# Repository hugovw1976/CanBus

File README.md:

# CanBus
Wireless Control CanBus Electrical System for 1976 VW Bug.
NRF24L01 With ATmega328p Wireless control for car electrical system.
Transmitter run on ATmega 328p running on low power mode 1mhz: https://forum.mysensors.org/topic/3018/tutorial-how-to-burn-1mhz-8mhz-bootloader-using-arduino-ide-1-6-5-r5/2
Receiver run on Teensy 3.2 with SN65HVD230 transceiver, module communicate with front/rear/midle modules over CanBus
CanBus Modules run on Teensy 3.2 with SN65HVD230 transceiver.
Wiper control over LinBus (motor from BMW) LIN library from: https://github.com/gandrewstone/LIN/blob/master/LIN.ino
  
  Transmitter:

<a data-flickr-embed="true" data-context="true"  href="https://www.flickr.com/photos/r42bug/39444284152/in/dateposted/" title="20171224_134232">

Receiver:

Can modules:

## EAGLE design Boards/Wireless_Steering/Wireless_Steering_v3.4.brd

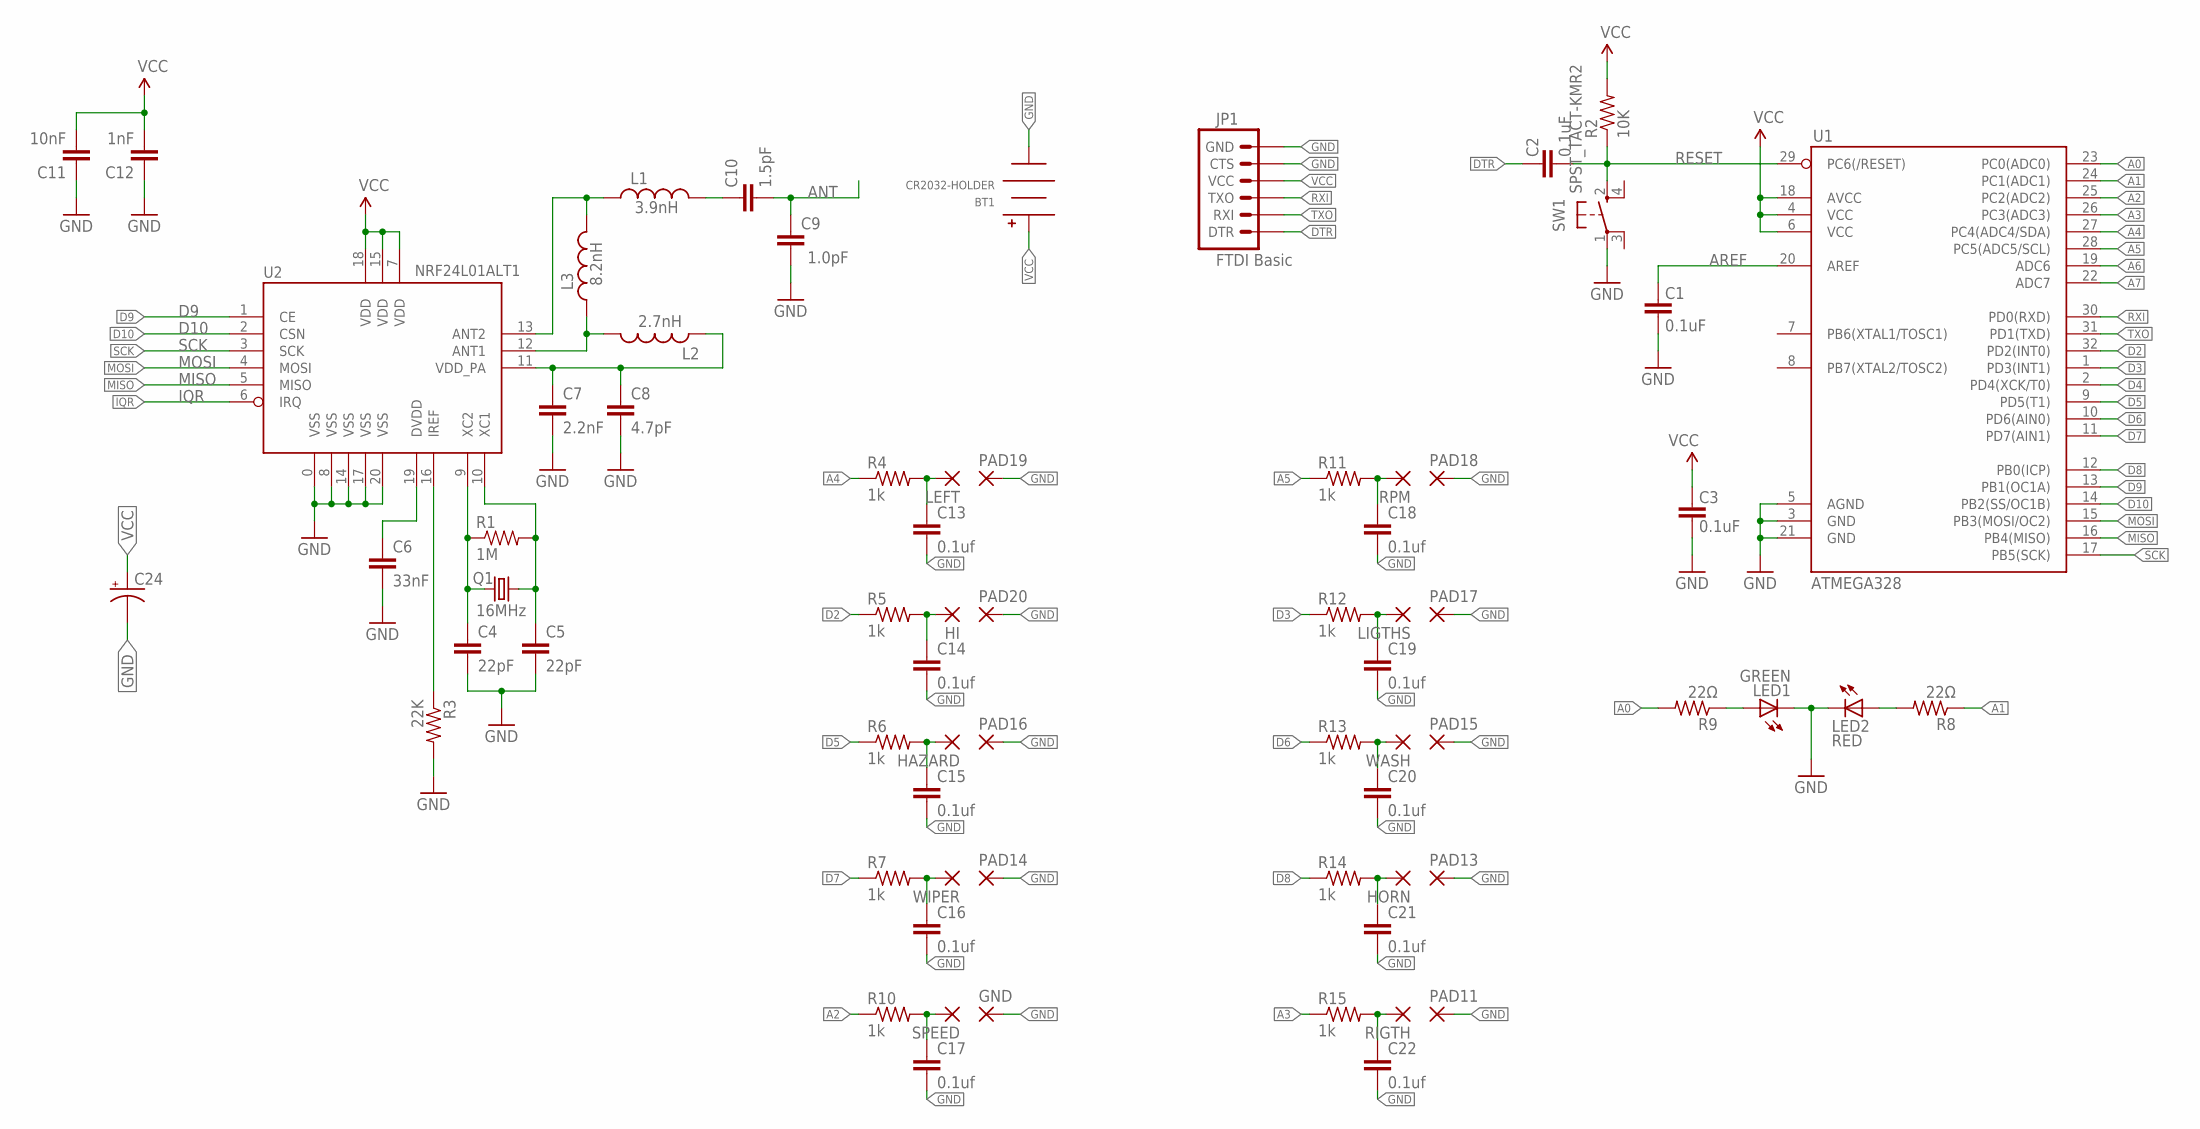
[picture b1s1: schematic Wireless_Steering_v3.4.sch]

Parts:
BT1: CR2032-HOLDER; CH28-2032LF
C1, C2, C3: 0.1uF; 0402-CAP
C4, C5: 22pF; 0402-CAP
C6: 33nF; 0402-CAP
C7: 2.2nF; 0402-CAP
C8: 4.7pF; 0402-CAP
C9: 1.0pF; 0402-CAP
C10: 1.5pF; 0402-CAP
C11: 10nF; 0402-CAP
C12: 1nF; 0402-CAP
C13, C14, C15, C16, C17, C18, C19, C20, C21, C22: 0.1uf; 0402-CAP
C24: CAP_POL1206; EIA3216
GND: SMD2; SMD1,27-2,54
HAZARD: SMD2; SMD1,27-2,54
HI: SMD2; SMD1,27-2,54
HORN: SMD2; SMD1,27-2,54
JP1: FTDI Basic; 1X06
L1: 3.9nH; C0402
L2: 2.7nH; C0402
L3: 8.2nH; C0402
LED1: GREEN; CHIP-LED0603
LED2: RED; CHIP-LED0603
LEFT: SMD2; SMD1,27-2,54
LIGTHS: SMD2; SMD1,27-2,54
PAD11, PAD13, PAD14, PAD15, PAD16, PAD17, PAD18, PAD19, PAD20: SMD2; SMD1,27-2,54
Q1: 16MHz; CRYSTAL-SMD-5X3
R1: 1M; 0402-RES
R2: 10K; 0402-RES
R3: 22K; 0402-RES
R4, R5, R6, R7, R10, R11, R12, R13, R14, R15: 1k; R0402
R8, R9: 22Ω; R0402
RIGTH: SMD2; SMD1,27-2,54
RPM: SMD2; SMD1,27-2,54
SPEED: SMD2; SMD1,27-2,54
SW1: SPST_TACT-KMR2; KMR2
U1: ATMEGA328; TQFP32-08
U2: NRF24L01ALT1; QFN20_ALT1
WASH: SMD2; SMD1,27-2,54
WIPER: SMD2; SMD1,27-2,54

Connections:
A0: R9.2, U1.23 (PC0(ADC0))
A1: R8.1, U1.24 (PC1(ADC1))
A2: R10.1, U1.25 (PC2(ADC2))
A3: R15.1, U1.26 (PC3(ADC3))
A4: R4.1, U1.27 (PC4(ADC4/SDA))
A5: R11.1, U1.28 (PC5(ADC5/SCL))
A6: U1.19 (ADC6)
A7: U1.22 (ADC7)
ANT: C9.2, C10.2
AREF: C1.2, U1.20 (AREF)
D2: R5.1, U1.32 (PD2(INT0))
D3: R12.1, U1.1 (PD3(INT1))
D4: U1.2 (PD4(XCK/T0))
D5: R6.1, U1.9 (PD5(T1))
D6: R13.1, U1.10 (PD6(AIN0))
D7: R7.1, U1.11 (PD7(AIN1))
D8: R14.1, U1.12 (PB0(ICP))
D9: U1.13 (PB1(OC1A)), U2.1 (CE)
D10: U1.14 (PB2(SS/OC1B)), U2.2 (CSN)
DTR: C2.2, JP1.1 (DTR)
GND: BT1.NEG, C1.1, C3.1, C4.2, C5.2, C6.2, C7.2, C8.2, C9.1, C11.1, C12.1, C13.2, C14.2, C15.2, C16.2, C17.2, C18.2, C19.2, C20.2, C21.2, C22.2, C24.C (-), GND.1, JP1.5 (CTS), JP1.6 (GND), LED1.C, LED2.C, PAD11.1, PAD13.1, PAD14.1, PAD15.1, PAD16.1, PAD17.1, PAD18.1, PAD19.1, PAD20.1, R3.2, SW1.1, U1.3 (GND), U1.5 (AGND), U1.21 (GND), U2.0 (VSS), U2.8 (VSS), U2.14 (VSS), U2.17 (VSS), U2.20 (VSS)
IQR: U2.6 (IRQ)
MISO: U1.16 (PB4(MISO)), U2.5 (MISO)
MOSI: U1.15 (PB3(MOSI/OC2)), U2.4 (MOSI)
unnamed: C4.1, Q1.1, R1.1, U2.9 (XC2)
unnamed: C5.1, Q1.3 (2), R1.2, U2.10 (XC1)
unnamed: L1.1, L3.2, U2.13 (ANT2)
unnamed: LED2.A, R8.2
unnamed: LED1.A, R9.1
unnamed: C7.1, C8.1, L2.1, U2.11 (VDD_PA)
unnamed: R3.1, U2.16 (IREF)
unnamed: C6.1, U2.19 (DVDD)
unnamed: L2.2, L3.1, U2.12 (ANT1)
unnamed: C10.1, L1.2
unnamed: C13.1, LEFT.1, R4.2
unnamed: C14.1, HI.1, R5.2
unnamed: C16.1, R7.2, WIPER.1
unnamed: C17.1, R10.2, SPEED.1
unnamed: C22.1, R15.2, RIGTH.1
unnamed: C21.1, HORN.1, R14.2
unnamed: C20.1, R13.2, WASH.1
unnamed: C19.1, LIGTHS.1, R12.2
unnamed: C18.1, R11.2, RPM.1
unnamed: C15.1, HAZARD.1, R6.2
RESET: C2.1, R2.1, SW1.2 (S), U1.29 (PC6(/RESET))
RXI: JP1.3 (TXO), U1.30 (PD0(RXD))
SCK: U1.17 (PB5(SCK)), U2.3 (SCK)
TXO: JP1.2 (RXI), U1.31 (PD1(TXD))
VCC: BT1.POS, C3.2, C11.2, C12.2, C24.A (+), JP1.4 (VCC), R2.2, U1.4 (VCC), U1.6 (VCC), U1.18 (AVCC), U2.7 (VDD), U2.15 (VDD), U2.18 (VDD)

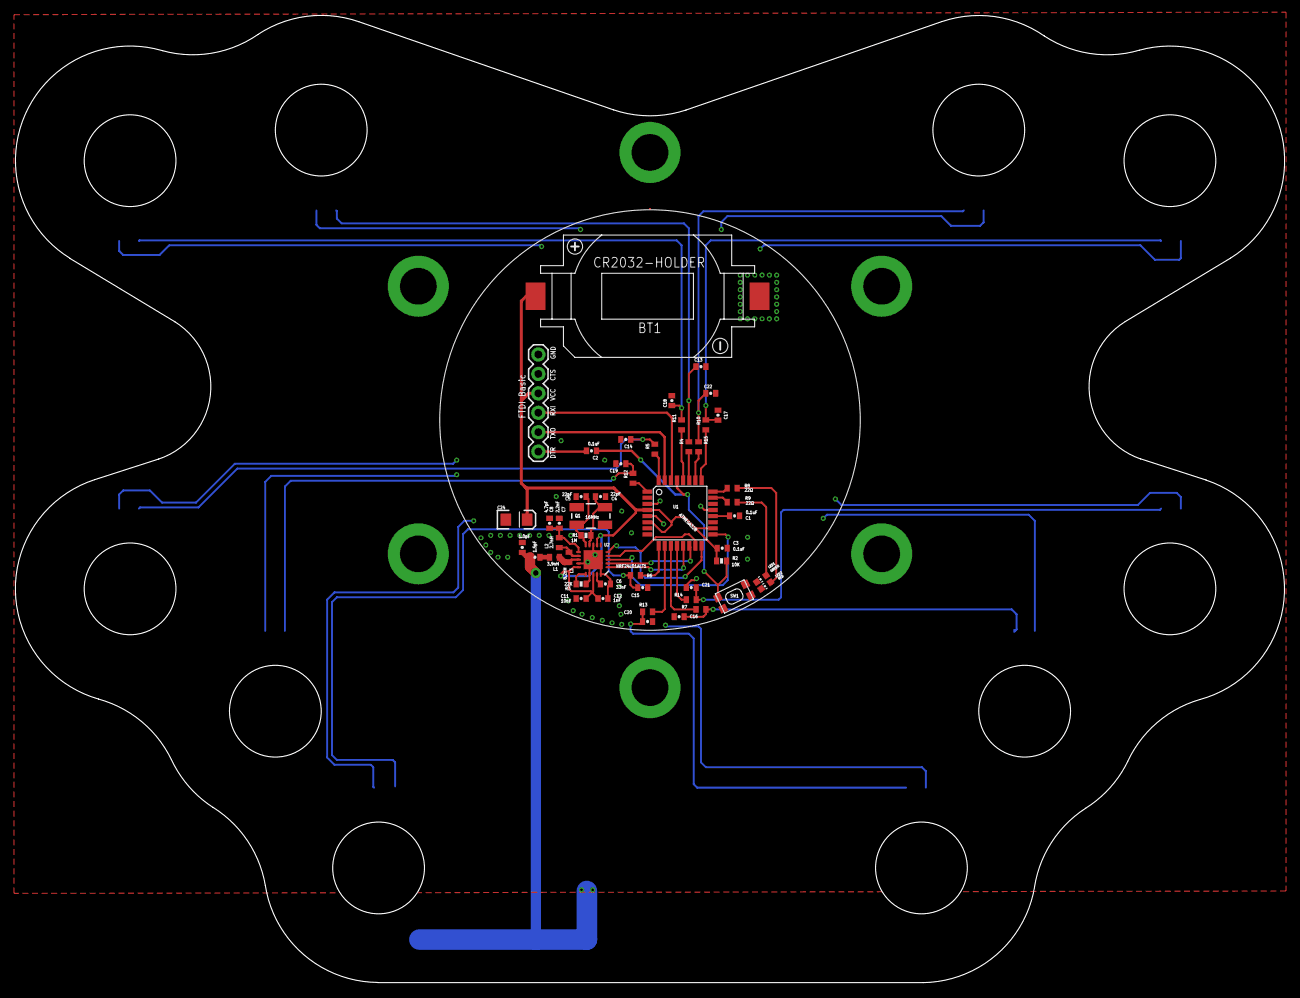
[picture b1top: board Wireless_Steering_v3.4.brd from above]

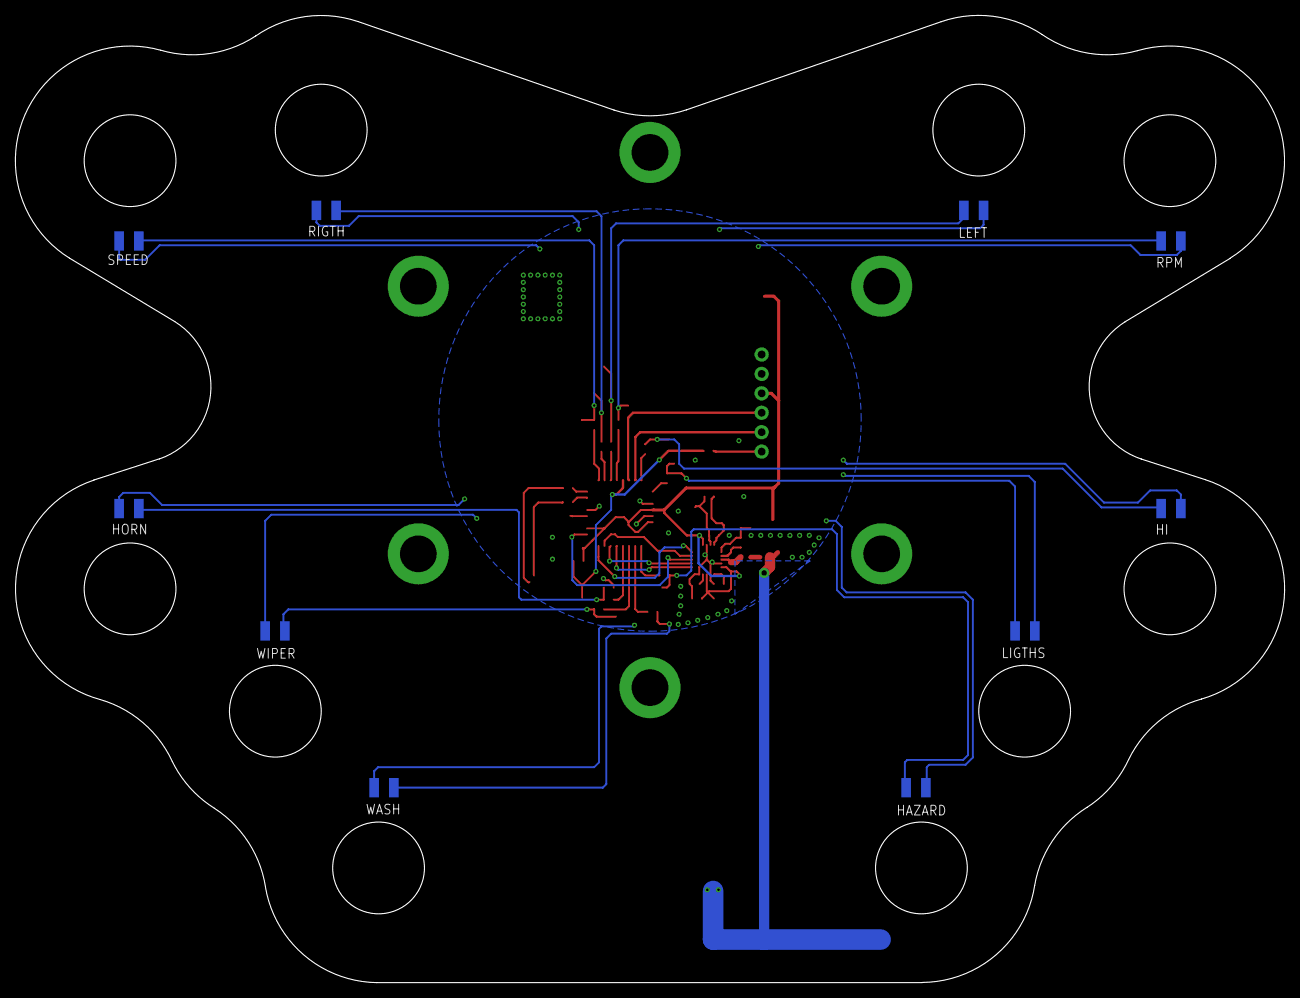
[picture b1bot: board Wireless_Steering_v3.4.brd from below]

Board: 2 copper layers, 166.0 x 126.5 mm, 69 parts (20 on the bottom side), 45 nets.

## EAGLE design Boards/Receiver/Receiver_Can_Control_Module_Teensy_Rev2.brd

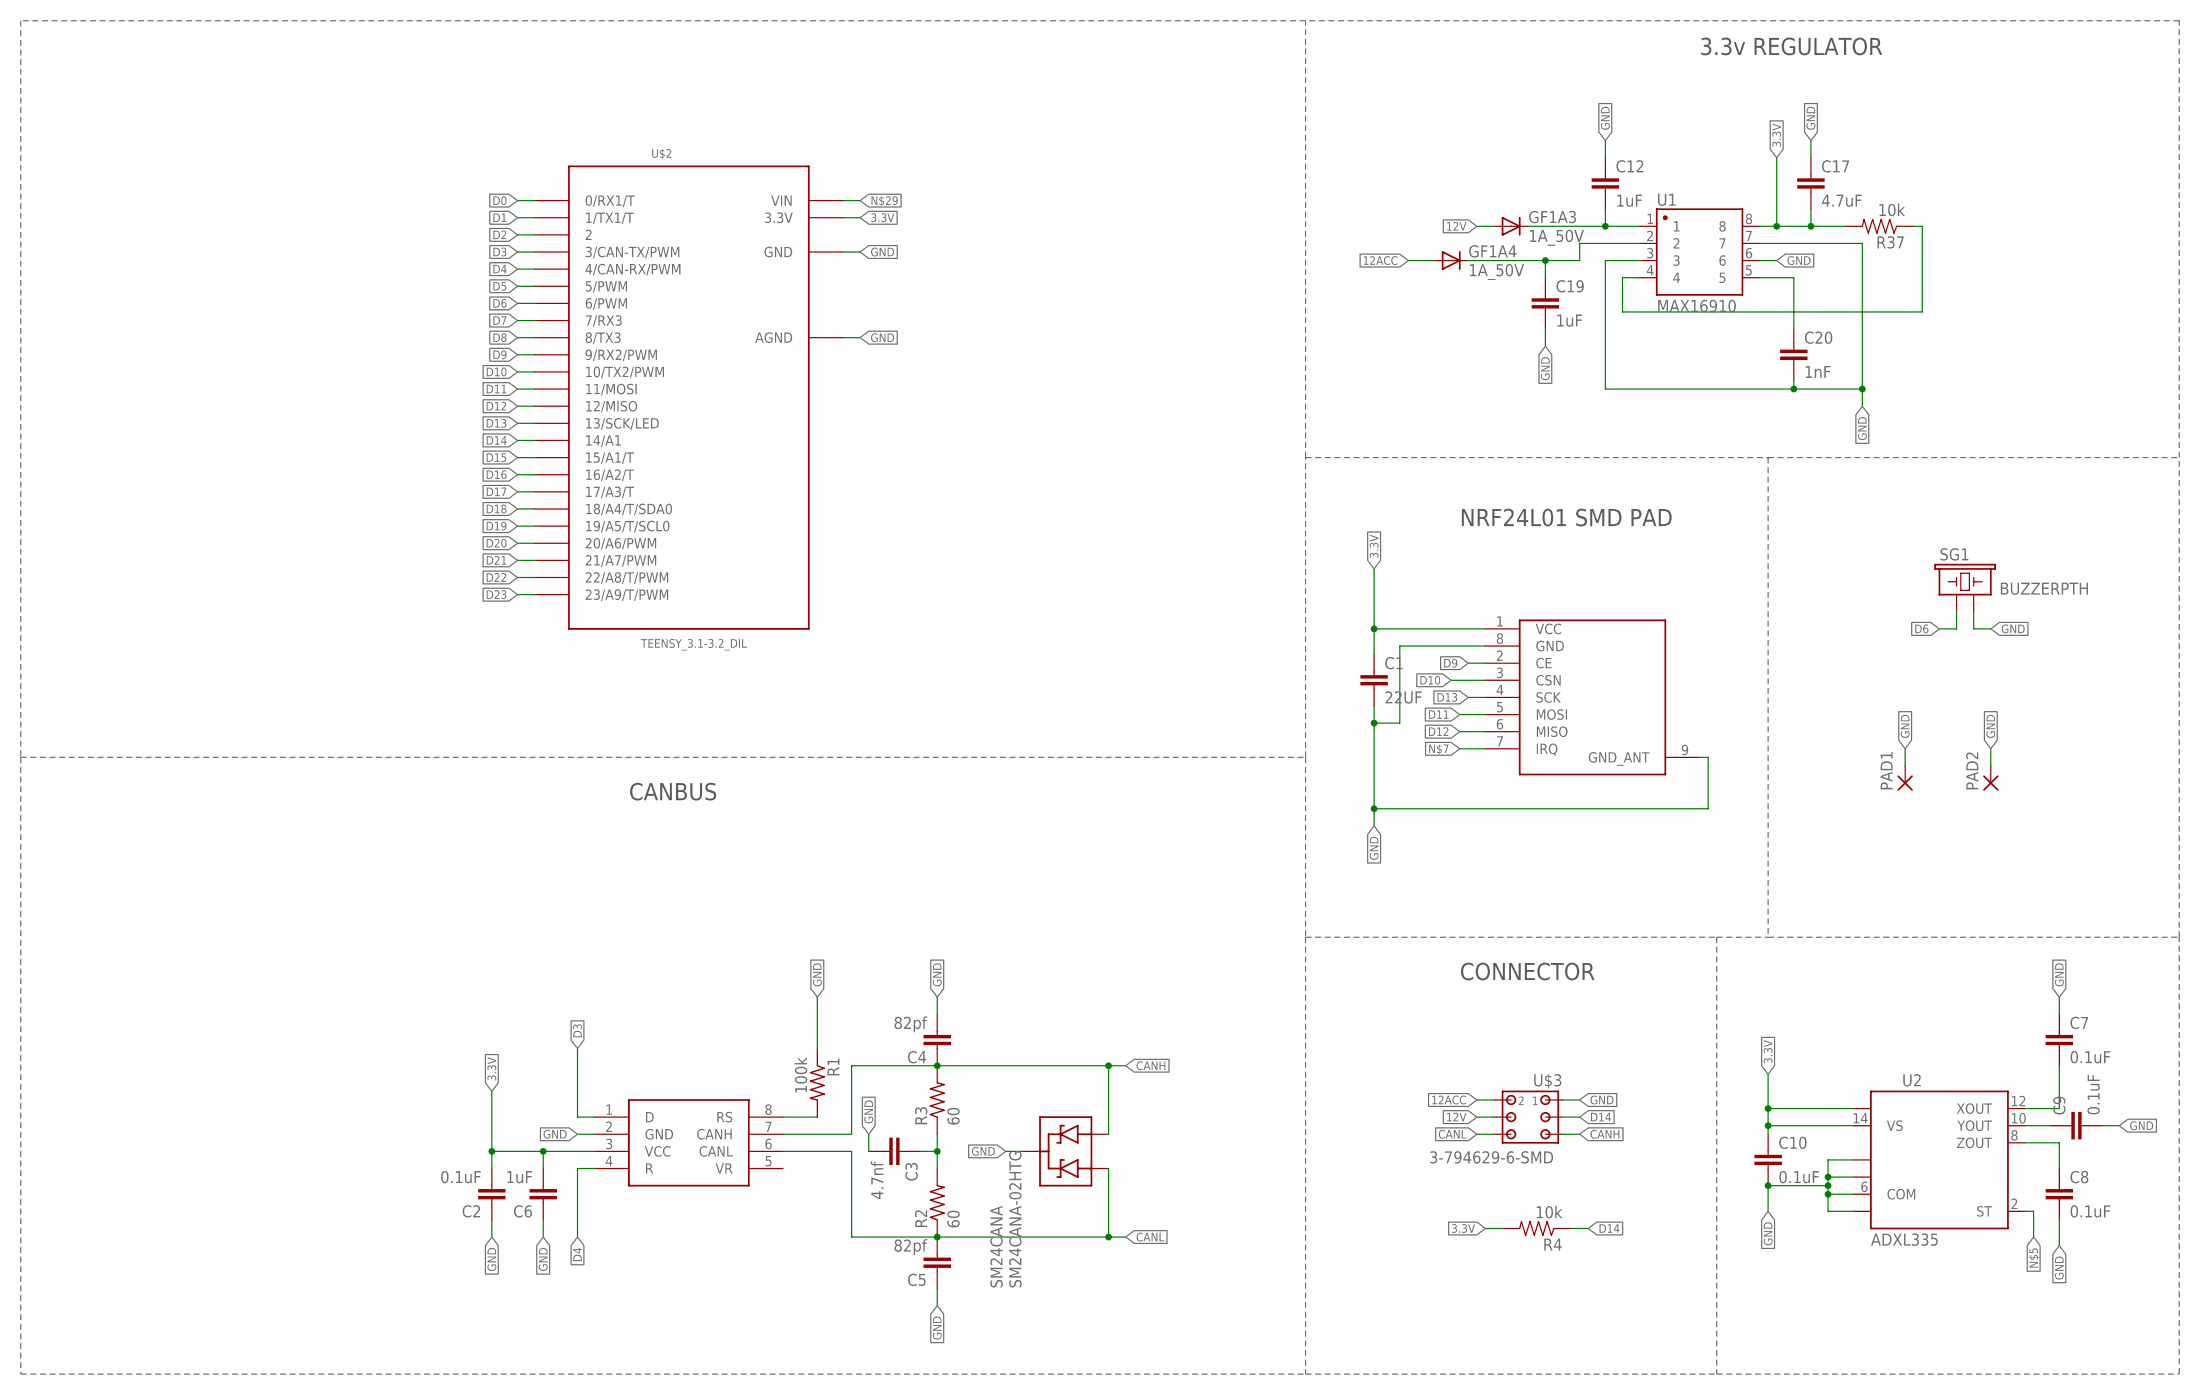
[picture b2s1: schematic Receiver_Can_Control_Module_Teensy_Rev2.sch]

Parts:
C1: 22UF; 1206
C2, C7, C8, C9, C10: 0.1uF; 0603-CAP
C3: 4.7nf; 0603-CAP
C4, C5: 82pf; 0603-CAP
C6: 1uF; 0603-CAP
C12, C19: 1uF; 0805
C17: 4.7uF; 0805
C20: 1nF; 0805
GF1A3, GF1A4: 1A_50V; DO-214AC
PAD1, PAD2: SMD2; SMD1,27-2,54
R1: 100k; R0402
R2, R3: 60; R0402
R4, R37: 10k; 0603-RES
SG1: BUZZERPTH; BUZZER-12MM
SM24CANA: SM24CANA-02HTG; SOT23-3
U1: MAX16910; SO08
U2: ADXL335; LFCSP-16
U$1: NRF24L01_PAD2; NRF24-2
U$2: TEENSY_3.1-3.2_DIL; TEENSY_3.0-3.2&LC_DIL
U$3: 3-794629-6-SMD; 3-794629-6
VP230: UP230; SO08

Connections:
3.3V: C1.1, C2.2, C6.2, C10.1, C17.2, R4.2, R37.2, U1.8, U2.14 (VS), U2.15 (VS), U$1.1 (VCC), U$2.3.3V, VP230.3 (VCC)
12ACC: GF1A4.A, U$3.2
12V: GF1A3.A, U$3.4
CANH: C4.1, R3.2, SM24CANA.2 (A2), U$3.5, VP230.7 (CANH)
CANL: C5.2, R2.1, SM24CANA.1 (A1), U$3.6, VP230.6 (CANL)
D0: U$2.0 (0/RX1/T)
D1: U$2.1 (1/TX1/T)
D2: U$2.2
D3: U$2.3 (3/CAN-TX/PWM), VP230.1 (D)
D4: U$2.4 (4/CAN-RX/PWM), VP230.4 (R)
D5: U$2.5 (5/PWM)
D6: SG1.+ (1), U$2.6 (6/PWM)
D7: U$2.7 (7/RX3)
D8: U$2.8 (8/TX3)
D9: U$1.2 (CE), U$2.9 (9/RX2/PWM)
D10: U$1.3 (CSN), U$2.10 (10/TX2/PWM)
D11: U$1.5 (MOSI), U$2.11 (11/MOSI)
D12: U$1.6 (MISO), U$2.12 (12/MISO)
D13: U$1.4 (SCK), U$2.13 (13/SCK/LED)
D14: R4.1, U$2.14/A0 (14/A1), U$3.3
D15: U$2.15/A1 (15/A1/T)
D16: U$2.16/A2 (16/A2/T)
D17: U$2.17/A3 (17/A3/T)
D18: U$2.18/A4 (18/A4/T/SDA0)
D19: U$2.19/A5 (19/A5/T/SCL0)
D20: U$2.20/A6 (20/A6/PWM)
D21: C7.2, U2.12 (XOUT), U$2.21/A7 (21/A7/PWM)
D22: C9.1, U2.10 (YOUT), U$2.22/A8 (22/A8/T/PWM)
D23: C8.1, U2.8 (ZOUT), U$2.23/A9 (23/A9/T/PWM)
GND: C1.2, C2.1, C3.2, C4.2, C5.1, C6.1, C7.1, C8.2, C9.2, C10.2, C12.1, C17.1, C19.2, C20.2, PAD1.1, PAD2.1, R1.1, SG1.- (2), SM24CANA.3 (C), U1.3, U1.6, U1.7, U2.3 (COM), U2.5 (COM), U2.6 (COM), U2.7 (COM), U$1.8 (GND), U$1.9 (GND_ANT), U$2.AGND, U$2.GND, U$3.1, VP230.2 (GND)
unnamed: C12.2, GF1A3.C, U1.1
unnamed: C19.1, GF1A4.C, U1.2
unnamed: R37.1, U1.4
unnamed: C20.1, U1.5
unnamed: R1.2, VP230.8 (RS)
unnamed: C3.1, R2.2, R3.1

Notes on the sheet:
CANBUS
CONNECTOR
NRF24L01 SMD PAD
3.3v REGULATOR

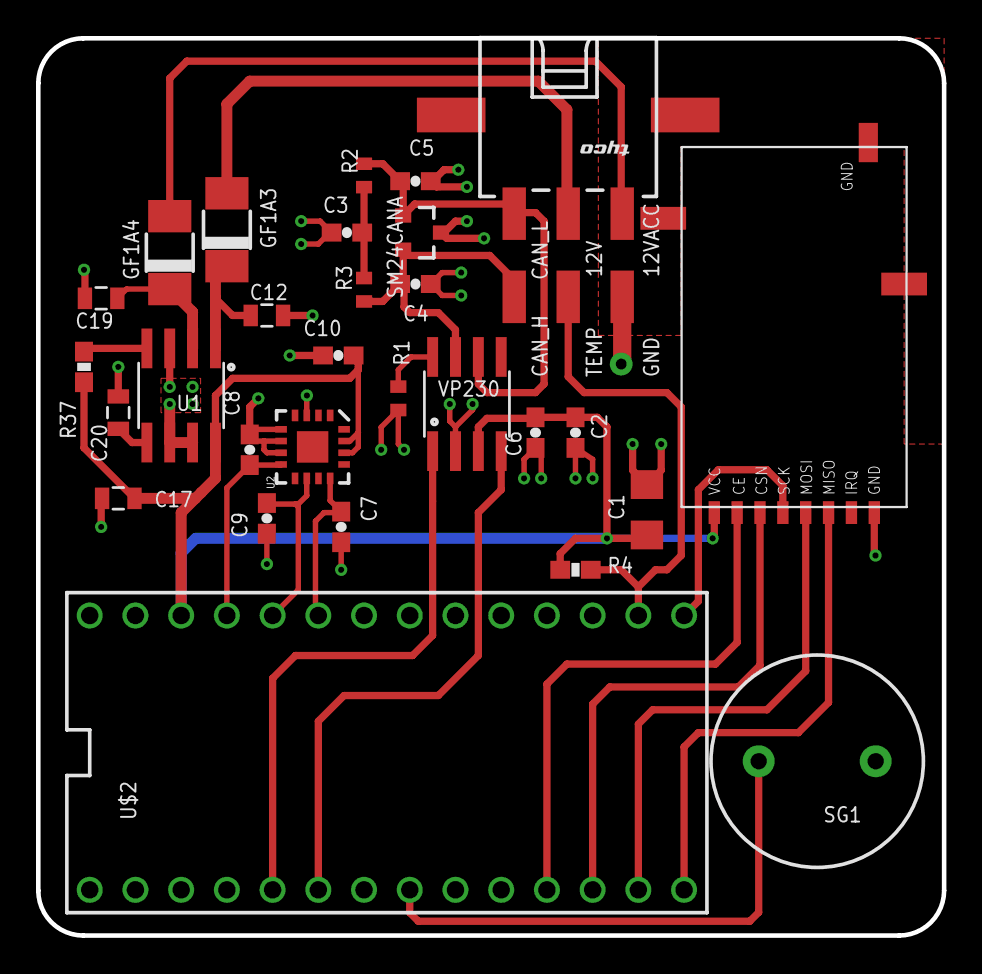
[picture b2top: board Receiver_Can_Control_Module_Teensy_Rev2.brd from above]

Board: 2 copper layers, 50.3 x 49.8 mm, 31 parts (0 on the bottom side), 24 nets.

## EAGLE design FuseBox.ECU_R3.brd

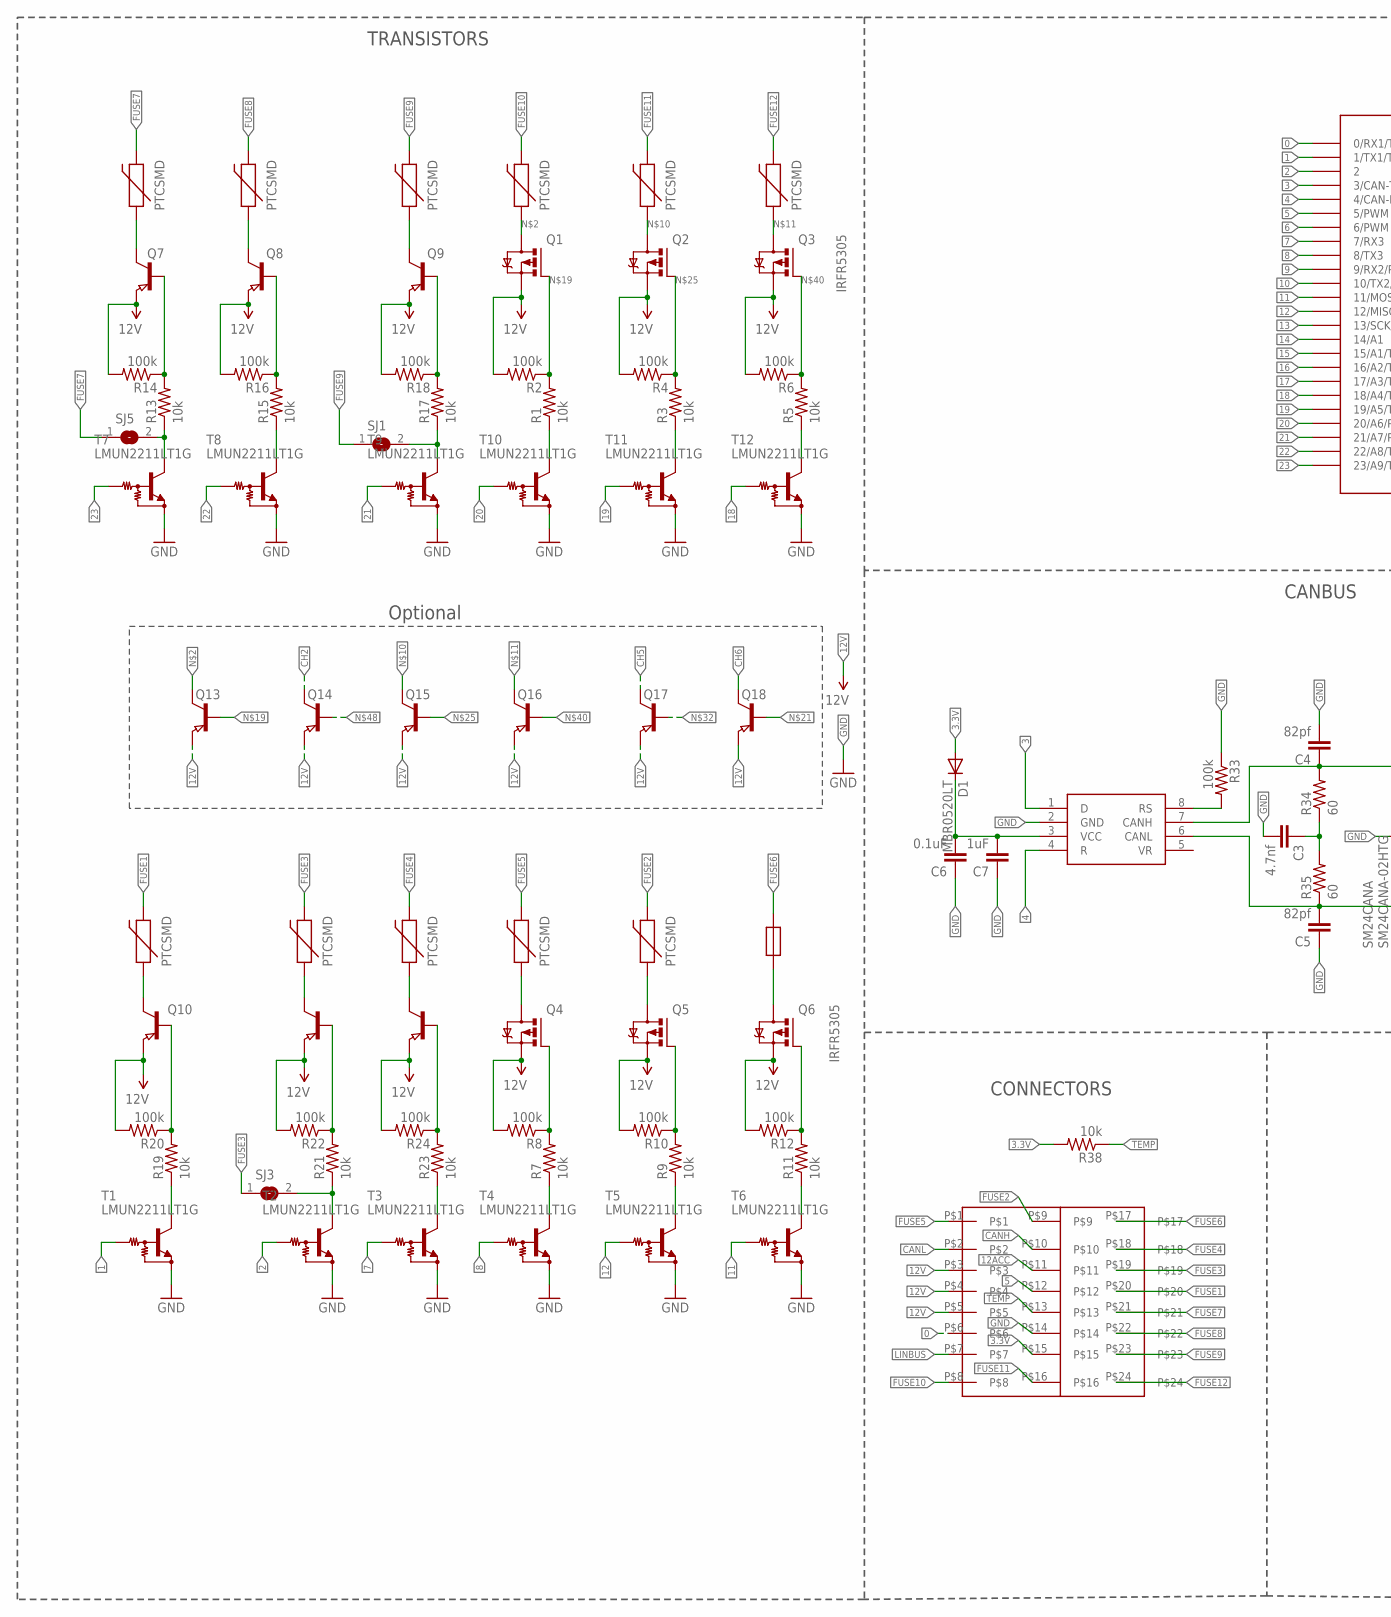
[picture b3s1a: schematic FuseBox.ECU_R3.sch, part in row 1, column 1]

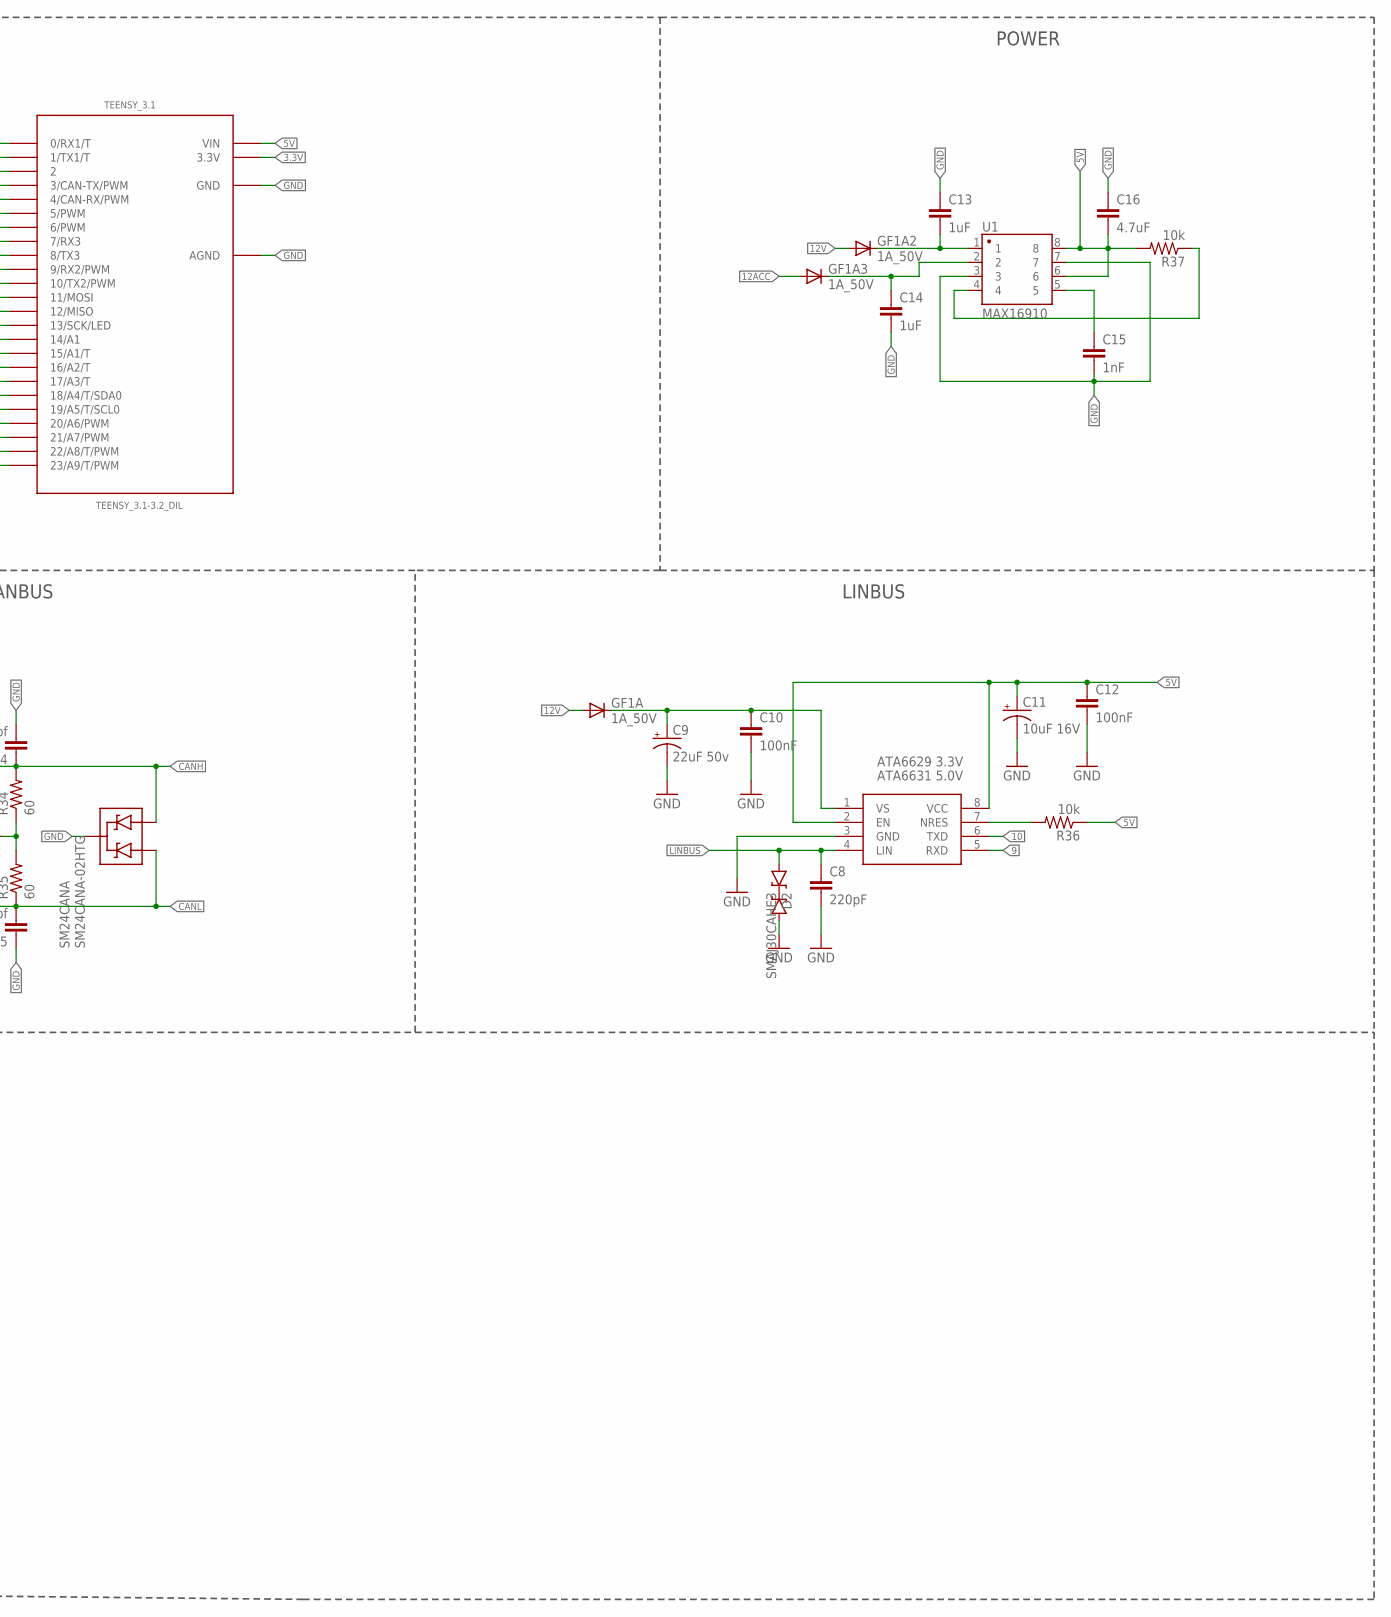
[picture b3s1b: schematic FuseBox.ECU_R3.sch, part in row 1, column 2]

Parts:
ATA6631: ATA6631; S08
C3: 4.7nf; 0603-CAP
C4, C5: 82pf; 0603-CAP
C6: 0.1uF; 0603-CAP
C7: 1uF; 0603-CAP
C8: 220pF; 0603-CAP
C9: 22uF 50v; PANASONIC_D
C10, C12: 100nF; 0603-CAP
C11: 10uF 16V; EIA3216
C13, C14: 1uF; 0805
C15: 1nF; 0805
C16: 4.7uF; 0805
D1: MBR0520LT; SOD123
D2: SMAJ30CAHE3; SMA-DIODE
F1, F2, F3, F4, F5, F6, F7, F8, F9, F10, F11: PTCSMD; PTC-1206
GF1A, GF1A2, GF1A3: 1A_50V; DO-214AC
Q1, Q2, Q3, Q4, Q5, Q6: IRFR5305; D-PAK_TO252AA
Q7, Q8, Q9, Q10, Q11, Q12, Q13, Q14, Q15, Q16, Q17, Q18: PNP-TRANSISTOR_SOT23; SOT23
R1, R3, R5, R7, R9, R11, R13, R15, R17, R19, R21, R23, R38: 10k; R0402
R2, R4, R6, R8, R10, R12, R14, R16, R18, R20, R22, R24, R33: 100k; R0402
R34, R35: 60; R0402
R36, R37: 10k; 0603-RES
SJ1, SJ3, SJ5: SJ
SM24CANA: SM24CANA-02HTG; SOT23-3
T1, T2, T3, T4, T5, T6, T7, T8, T9, T10, T11, T12: LMUN2211LT1G; SOT23
TEENSY_3.1: TEENSY_3.1-3.2_DIL; TEENSY_3.0-3.2&LC_DIL
U1: MAX16910; SO08
U$2: RESETTABLE_1210; 1210
U$3: HCCPHPE24BKA90F
VP230: UP230; SO08

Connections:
0: TEENSY_3.1.0 (0/RX1/T), U$3.P$6
1: T1.1 (B), TEENSY_3.1.1 (1/TX1/T)
2: T2.1 (B), TEENSY_3.1.2
3: TEENSY_3.1.3 (3/CAN-TX/PWM), VP230.1 (D)
3.3V: D1.A, R38.2, TEENSY_3.1.3.3V, U$3.P$15
4: TEENSY_3.1.4 (4/CAN-RX/PWM), VP230.4 (R)
5: TEENSY_3.1.5 (5/PWM), U$3.P$12
5V: ATA6631.2 (EN), ATA6631.8 (VCC), C11.A (+), C12.1, C16.2, R36.1, R37.2, TEENSY_3.1.VIN, U1.6, U1.8
6: TEENSY_3.1.6 (6/PWM)
7: T3.1 (B), TEENSY_3.1.7 (7/RX3)
8: T4.1 (B), TEENSY_3.1.8 (8/TX3)
9: ATA6631.5 (RXD), TEENSY_3.1.9 (9/RX2/PWM)
10: ATA6631.6 (TXD), TEENSY_3.1.10 (10/TX2/PWM)
11: T6.1 (B), TEENSY_3.1.11 (11/MOSI)
12: T5.1 (B), TEENSY_3.1.12 (12/MISO)
12ACC: GF1A3.A, U$3.P$11
12V: GF1A.A, GF1A2.A, Q1.3 (S), Q2.3 (S), Q3.3 (S), Q4.3 (S), Q5.3 (S), Q6.3 (S), Q7.2 (E), Q8.2 (E), Q9.2 (E), Q10.2 (E), Q11.2 (E), Q12.2 (E), Q13.2 (E), Q14.2 (E), Q15.2 (E), Q16.2 (E), Q17.2 (E), Q18.2 (E), R2.2, R4.2, R6.2, R8.2, R10.2, R12.2, R14.2, R16.2, R18.2, R20.2, R22.2, R24.2, U$3.P$3, U$3.P$4, U$3.P$5
13: TEENSY_3.1.13 (13/SCK/LED)
14: TEENSY_3.1.14/A0 (14/A1)
15: TEENSY_3.1.15/A1 (15/A1/T)
16: TEENSY_3.1.16/A2 (16/A2/T)
17: TEENSY_3.1.17/A3 (17/A3/T)
18: T12.1 (B), TEENSY_3.1.18/A4 (18/A4/T/SDA0)
19: T11.1 (B), TEENSY_3.1.19/A5 (19/A5/T/SCL0)
20: T10.1 (B), TEENSY_3.1.20/A6 (20/A6/PWM)
21: T9.1 (B), TEENSY_3.1.21/A7 (21/A7/PWM)
22: T8.1 (B), TEENSY_3.1.22/A8 (22/A8/T/PWM)
23: T7.1 (B), TEENSY_3.1.23/A9 (23/A9/T/PWM)
CANH: C4.1, R34.2, SM24CANA.2 (A2), U$3.P$10, VP230.7 (CANH)
CANL: C5.2, R35.1, SM24CANA.1 (A1), U$3.P$2, VP230.6 (CANL)
CH2: F1.1, Q5.4 (D), Q14.3 (C)
CH5: F2.1, Q4.4 (D), Q17.3 (C)
CH6: Q6.4 (D), Q18.3 (C), U$2.P$1
CH7: F6.1, Q7.3 (C)
CH8: F7.1, Q8.3 (C)
CH9: F8.1, Q9.3 (C)
FUSE1: F5.2, U$3.P$20
FUSE2: F1.2, U$3.P$9
FUSE3: F4.2, SJ3.1, U$3.P$19
FUSE4: F3.2, U$3.P$18
FUSE5: F2.2, U$3.P$1
FUSE6: U$2.P$2, U$3.P$17
FUSE7: F6.2, SJ5.1, U$3.P$21
FUSE8: F7.2, U$3.P$22
FUSE9: F8.2, SJ1.1, U$3.P$23
FUSE10: F9.2, U$3.P$8
FUSE11: F10.2, U$3.P$16
FUSE12: F11.2, U$3.P$24
GND: ATA6631.3 (GND), C3.2, C4.2, C5.1, C6.1, C7.1, C8.2, C9.-, C10.2, C11.C (-), C12.2, C13.1, C14.2, C15.2, C16.1, D2.A, R33.1, SM24CANA.3 (C), T1.2 (E), T2.2 (E), T3.2 (E), T4.2 (E), T5.2 (E), T6.2 (E), T7.2 (E), T8.2 (E), T9.2 (E), T10.2 (E), T11.2 (E), T12.2 (E), TEENSY_3.1.AGND, TEENSY_3.1.GND, U1.3, U1.7, U$3.P$14, VP230.2 (GND)
LINBUS: ATA6631.4 (LIN), C8.1, D2.C (A1), U$3.P$7
unnamed: C6.2, C7.2, D1.C, VP230.3 (VCC)
unnamed: F9.1, Q1.4 (D), Q13.3 (C)
unnamed: R15.1, T8.3 (C)
unnamed: Q8.1 (B), R15.2, R16.1
unnamed: R13.1, SJ5.2, T7.3 (C)
unnamed: Q7.1 (B), R13.2, R14.1
unnamed: C13.2, GF1A2.C, U1.1
unnamed: R17.1, SJ1.2, T9.3 (C)
unnamed: F10.1, Q2.4 (D), Q15.3 (C)
unnamed: F11.1, Q3.4 (D), Q16.3 (C)
unnamed: C14.1, GF1A3.C, U1.2
unnamed: Q9.1 (B), R17.2, R18.1
unnamed: R1.1, T10.3 (C)
unnamed: Q1.1 (G), Q13.1 (B), R1.2, R2.1
unnamed: R11.1, T6.3 (C)
unnamed: Q6.1 (G), Q18.1 (B), R11.2, R12.1
unnamed: F5.1, Q10.3 (C)
unnamed: F4.1, Q11.3 (C)
unnamed: R3.1, T11.3 (C)
unnamed: Q2.1 (G), Q15.1 (B), R3.2, R4.1
unnamed: F3.1, Q12.3 (C)
unnamed: R23.1, T3.3 (C)
unnamed: Q12.1 (B), R23.2, R24.1
unnamed: R37.1, U1.4
unnamed: R7.1, T4.3 (C)
unnamed: Q4.1 (G), Q17.1 (B), R7.2, R8.1
unnamed: C15.1, U1.5
unnamed: R5.1, T12.3 (C)
unnamed: Q3.1 (G), Q16.1 (B), R5.2, R6.1
unnamed: R21.1, SJ3.2, T2.3 (C)
unnamed: Q11.1 (B), R21.2, R22.1
unnamed: R19.1, T1.3 (C)
unnamed: Q10.1 (B), R19.2, R20.1
unnamed: R9.1, T5.3 (C)
unnamed: Q5.1 (G), Q14.1 (B), R9.2, R10.1
unnamed: R33.2, VP230.8 (RS)
unnamed: ATA6631.1 (VS), C9.+, C10.1, GF1A.C
unnamed: ATA6631.7 (NRES), R36.2
unnamed: C3.1, R34.1, R35.2
TEMP: R38.1, U$3.P$13

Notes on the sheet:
ATA6631 5.0V
ATA6629 3.3V
Optional
TRANSISTORS
POWER
CANBUS
LINBUS
CONNECTORS

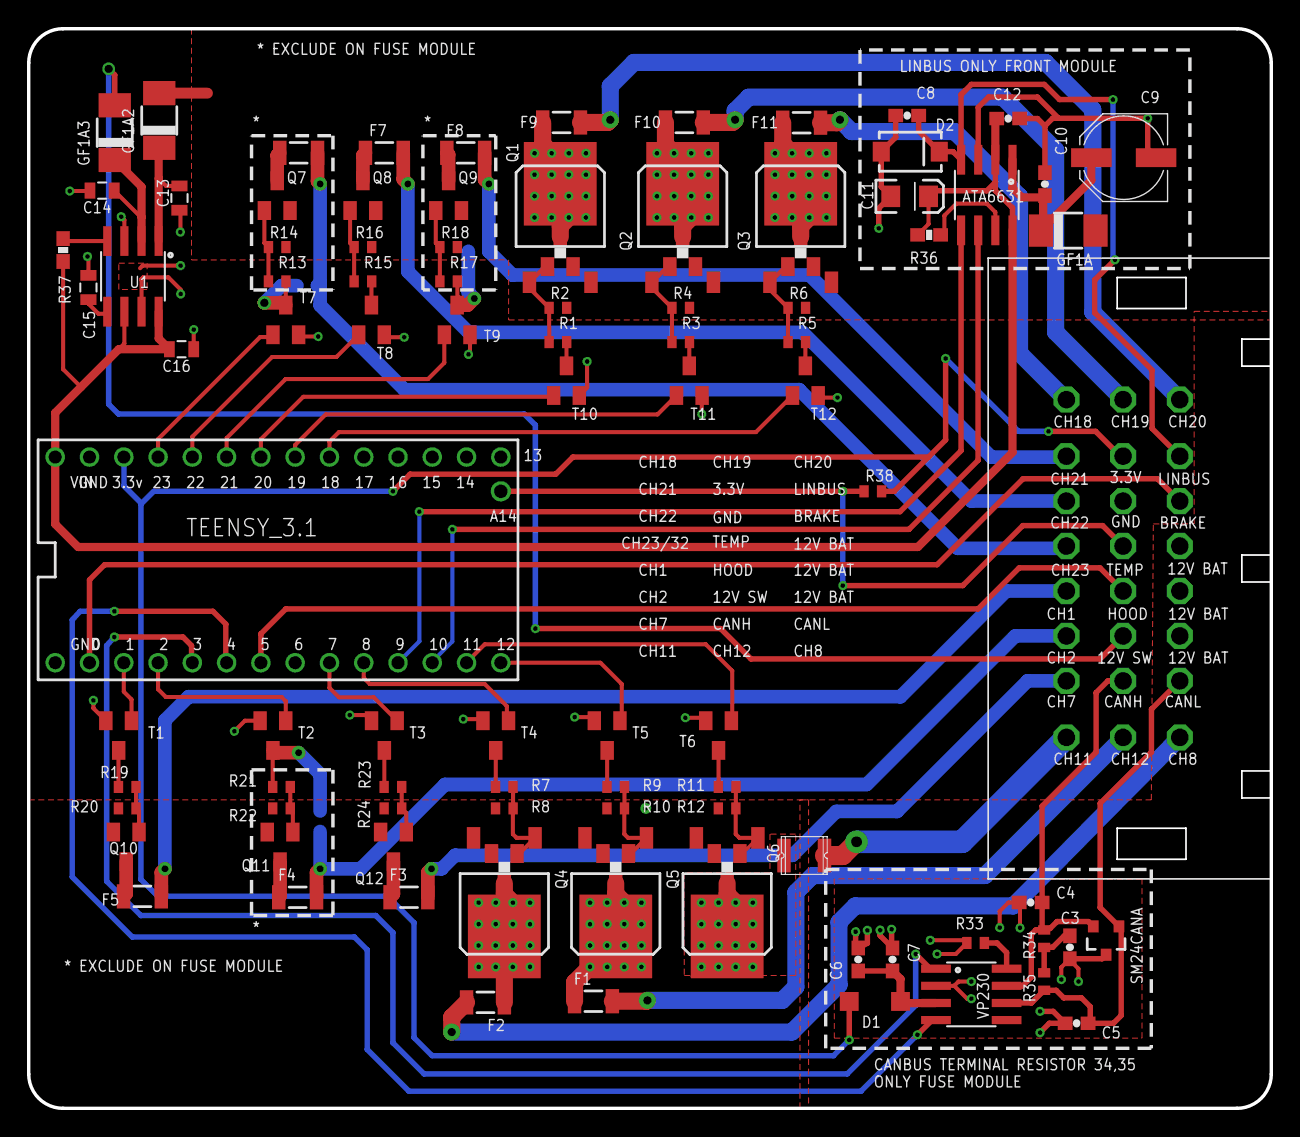
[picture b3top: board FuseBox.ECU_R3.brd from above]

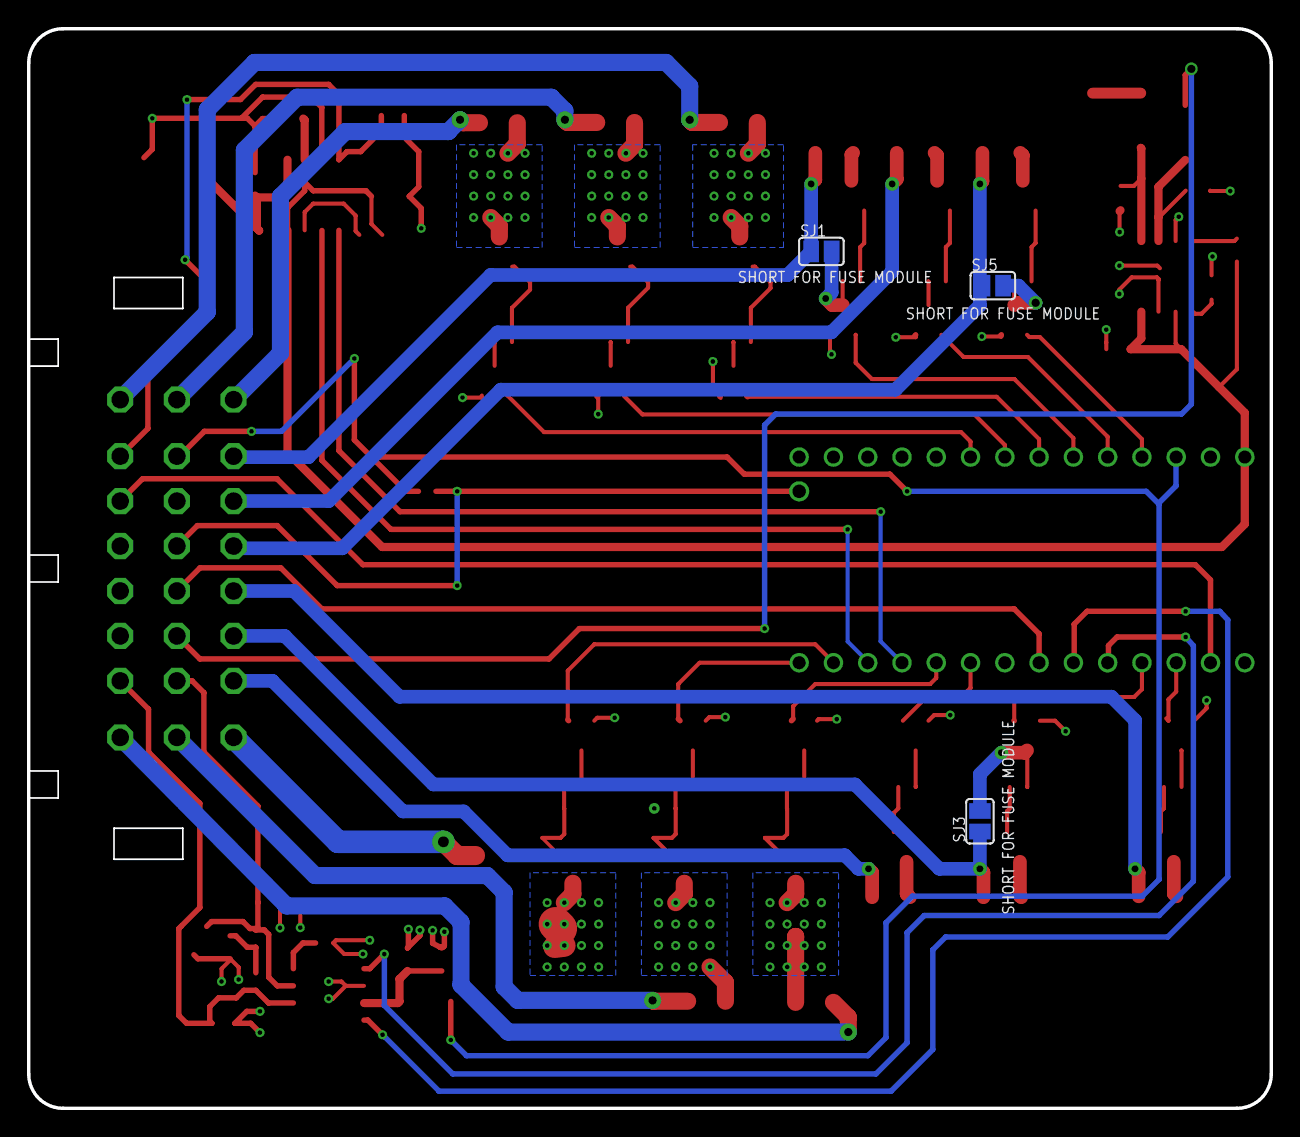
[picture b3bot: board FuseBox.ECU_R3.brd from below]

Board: 2 copper layers, 92.1 x 80.0 mm, 100 parts (3 on the bottom side), 84 nets.

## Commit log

2018-03-06 Create Pictures
2018-03-06 Update Pictures

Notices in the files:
parts and their libraries:
SparkFun-Aesthetics: Licensing: Creative Commons ShareAlike 4.0 International - https://creativecommons.org/licenses/by-sa/4.0
